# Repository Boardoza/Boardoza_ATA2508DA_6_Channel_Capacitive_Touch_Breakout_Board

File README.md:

# Boardoza ATA2508DA 6-Channel Capacitive Touch Breakout Board

The **Boardoza ATA2508DA Breakout Board** is a capacitive touch input module based on the **ATLab ATA2508DA digital touch controller**. It features six independent touch pads that detect finger contact through changes in capacitance, allowing users to interact with electronic systems without mechanical buttons. 

The board operates with a **3.3V or 5V** power supply and communicates with microcontrollers through an **I²C interface**. It also provides configurable digital I/O pins and a touch interrupt output, allowing integration with Arduino, ESP32, STM32, Raspberry Pi, and other embedded platforms. The board is suitable for **touch-based control panels, home automation, interactive electronics, and embedded user interfaces**.

| Front Side | Back Side |
|:---:|:---:|
|  |  |

---

## Key Features

- **6-Channel Capacitive Touch Detection:** Provides six independent touch-sensitive pads for implementing button-free input interfaces.
- **I²C Communication Interface:** Allows touch status and configuration registers to be accessed through a standard two-wire connection.
- **Programmable Touch Sensitivity:** Supports individual sensitivity adjustments for touch channels to accommodate different applications and operating conditions.
- **Automatic Impedance Calibration (AIC):** Helps maintain stable touch detection by compensating for changes in sensor characteristics.
- **Touch Interrupt Output:** Provides a dedicated interrupt signal to notify the host microcontroller when touch status changes.

---

## Technical Specifications

**Model:** ATA2508DA  
**Manufacturer:** Boardoza  
**Manufacturer IC:** ATLab  
**Input Voltage:** 3.3V - 5V  
**Interface:** I²C  
**Functions:** Capacitive Touch Detection  
**Touch Channels:** 6  
**Touch Sensitivity:** Programmable  
**Touch Strength Resolution:** 8-bit  
**Additional Features:** Automatic Impedance Calibration (AIC), Adjacent Pattern Interference Suppression (APIS)  
**Power Management:** Active, Idle, and Sleep Modes  
**Operating Temperature:** -35°C to +90°C     
**Board Dimensions:** 60mm x 60mm

---

## Board Pinout

### ( J1 ) Power, I²C Communication and Digital I/O Pins

| Pin Number | Pin Name | Description |
| :---: | :---: | --- |
| 1 | VCC | Power Supply (3.3V - 5V) |
| 2 | TINT | Touch Interrupt Output, signals changes in touch detection status |
| 3 | SCL | I²C Clock Input from Host Microcontroller |
| 4 | SDA | Bidirectional I²C Data Line |
| 5 | DIO_0 | Configurable Digital I/O, Direct Touch Output, or External Interrupt Input |
| 6 | DIO_8 | Configurable Digital I/O, Direct Touch Output, or External Interrupt Input |
| 7 | GND | Ground Connection |

---

## Board Dimensions

---

## Step Files

[Boardoza ATA2508DA.step](./assets/ATA2508DA%20Step.step)

---

## Sensor Datasheet

[ATA2508DA Datasheet.pdf](./assets/ATA2508DA%20Datasheet.pdf)

---

## Version History

- V1.0.0 - Initial Release

---

## Support

- If you have any questions or need support, please contact <support@boardoza.com>

---

## **License**

This repository contains both hardware and software components:

### **Hardware Design**

[![CC BY-SA 4.0][cc-by-sa-shield]][cc-by-sa]

All hardware design files are licensed under [Creative Commons Attribution-ShareAlike 4.0 International License][cc-by-sa].

[cc-by-sa]: http://creativecommons.org/licenses/by-sa/4.0/
[cc-by-sa-shield]: https://img.shields.io/badge/License-CC%20BY--SA%204.0-lightgrey.svg

### **Software/Firmware**

[![BSD-3-Clause][bsd-shield]][bsd]

All software and firmware are licensed under [BSD 3-Clause License][bsd].

[bsd]: https://opensource.org/licenses/BSD-3-Clause
[bsd-shield]: https://img.shields.io/badge/License-BSD%203--Clause-blue.svg

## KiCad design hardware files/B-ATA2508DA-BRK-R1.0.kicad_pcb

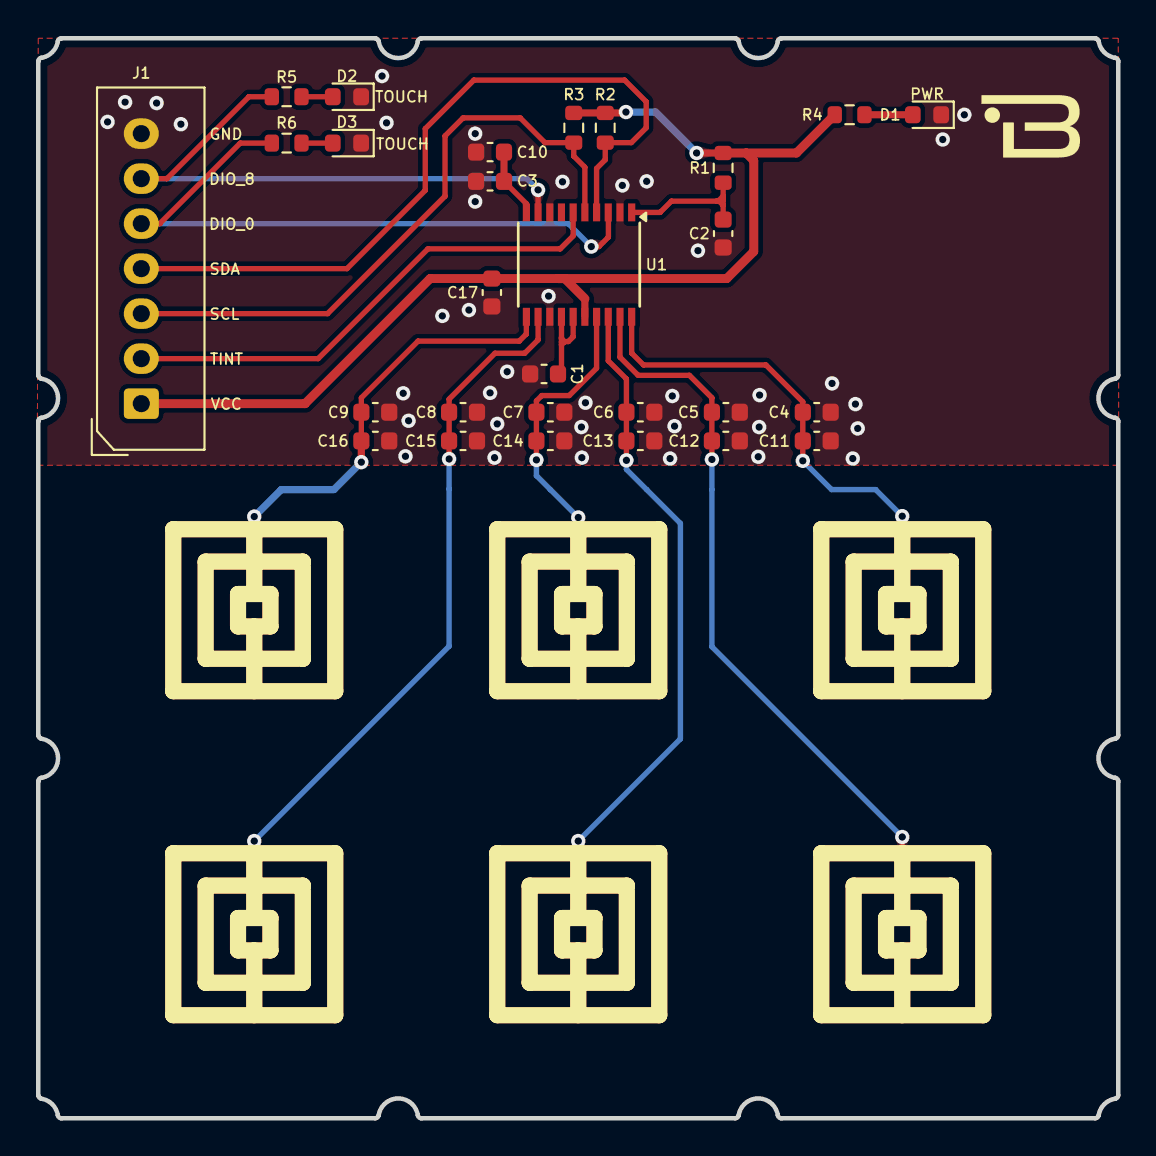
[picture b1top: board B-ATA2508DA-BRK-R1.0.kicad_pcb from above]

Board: 2 copper layers, 60.0 x 60.0 mm, 28 parts (0 on the bottom side), 19 nets.

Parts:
C1, C2: 10uF; C_0603_1608Metric
C3, C4, C5, C6, C7, C8, C9, C10, C11, C12, C13, C14, C15, C16: 7pF; C_0603_1608Metric
C17: 100nF; C_0603_1608Metric
D1, D2, D3: PWR; LED_0603_1608Metric
J1: Conn_01x07; 2317-07S_1x07_P2.50mm_Vertical
R1: 10K; R_0603_1608Metric
R2, R3: 2K; R_0603_1608Metric
R4, R5, R6: 330R; R_0603_1608Metric
U1: ATA2508DA-20S; SSOP-20_4.4x6.5mm_P0.65mm

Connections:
/DIO_0: J1.5, R6.1, U1.3 (DIO_0)
/DIO_8: J1.6, R5.1, U1.9 (DIO_8)
/S0: C4.1, C11.1, U1.20 (S0)
/S1: C5.1, C12.1, U1.19 (S1)
/S2: C6.1, C13.1, U1.18 (S2)
/S3: C7.1, C14.1, U1.17 (S3)
/S8: C8.1, C15.1, U1.12 (S8)
/S9: C9.1, C16.1, U1.11 (S9)
/SCL: J1.3, R3.2, U1.5 (SCL)
/SDA: J1.4, R2.2, U1.4 (SDA)
/TINT: J1.2, U1.6 (TINT)
/VCC: C17.2, J1.1, R1.1, R2.1, R3.1, R4.1, U1.16 (VPH)
GND: C1.2, C2.1, C3.2, C4.2, C5.2, C6.2, C7.2, C8.2, C9.2, C10.2, C11.2, C12.2, C13.2, C14.2, C15.2, C16.2, C17.1, D1.1 (K), D2.1 (K), D3.1 (K), J1.7, U1.2 (ID), U1.8 (TCLK), U1.13 (VSS)
unnamed: D1.2 (A), R4.2
unnamed: D2.2 (A), R5.2
unnamed: D3.2 (A), R6.2
unnamed: C3.1, C10.1, U1.10 (AREF)
unnamed: C2.2, R1.2, U1.1 (RESET_N)
unnamed: C1.1, U1.14 (V25), U1.15 (VLDO)
